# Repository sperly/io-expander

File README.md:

# RS485_IO8 I/O expansion board

An STM32G030-based Modbus RTU I/O expansion board with **8 isolated inputs**
and **8 configurable outputs**. A hardware strap selects RS-485 or RS-232
communication, and a USB-C port (CH340C virtual COM port) gives the same Modbus
link from a PC. Outputs support low-side, high-side, push-pull and PWM modes.

| Directory | Contents |
|---|---|
| [hardware/](hardware/README.md) | Revision B KiCad project, schematics, PCB layout, BOMs, generation and validation tools, and archived revision A files |
| [software/](software/README.md) | C11 firmware, portable Modbus and I/O logic, host unit tests, and a Python Modbus client |

Open `hardware/RS485_IO8.kicad_pro` in KiCad 9 or 10. See the
[hardware README](hardware/README.md) for wiring, straps, electrical limits
and design checks. The schematics are generated; make schematic changes
through the scripts in `hardware/tools/`.

To build and run the host unit tests, install CMake, Ninja and a native C
compiler, then run from the repository root:

```sh
cd software
cmake --preset host-tests
cmake --build --preset host-tests
ctest --preset host-tests
```

Firmware builds also require `arm-none-eabi-gcc` with newlib-nano and ST CMSIS
headers. See the [software README](software/README.md) for toolchain setup,
flashing, the register map and client examples.

The PCB is placed but not routed. The design and firmware have not yet been
tested on hardware; see the subdirectory READMEs for validation status and
remaining prototype checks.

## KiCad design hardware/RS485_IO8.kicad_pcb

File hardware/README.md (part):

# RS485_IO8 — revision B

**8 isolated inputs** (5–24 V, wired as sink or source) and **8 outputs**
(low-side, high-side, push-pull or PWM), with a host link that a strap
switches between **RS-485 (half duplex) and RS-232**, plus a **USB-C port**
(CH340C USB-serial) on the same UART. All parts are
available from LCSC. Open `RS485_IO8.kicad_pro` in KiCad 9 or 10. The
schematic has an overview page and five sheets; `RS485_IO8.pdf` is the
plotted copy.

Firmware: `../software` (Modbus RTU slave, CMake).

## What changed from rev A

| | rev A | rev B |
|---|---|---|
| Schematic | every pin ended in a net label | real wiring inside each functional block, framed blocks, notes and tables on every sheet, overview page with connector/strap tables |
| Host interface | THVD1410 (RS-485 only) | **MAX3160** multiprotocol transceiver, RS-485 or RS-232 set by the **MODE strap** |
| I/O split | 8 combined I/Os (driver output + non-isolated NPN read-back on the same terminal) | **8 dedicated outputs + 8 dedicated isolated inputs** |
| Inputs | 47k/22k + BC847 level shifter, 0–VIO only | **TLP290-4 bidirectional optocouplers**, 5–24 V, two isolated groups with their own COM, sink or source |
| Output driver | DRV8908-Q1 (not stocked at LCSC) | **DRV8912-Q1**, pin-compatible superset; OUT1–OUT8 used, OUT9–OUT12 unconnected |
| USB | – | **USB-C (J11) with CH340C** virtual COM port on the same UART; VBUS can power the board |
| Connectors | 2.54 mm pin headers | **2.54 mm screw terminals** (Xinya XY308) for 5 V, VIO, serial and all I/O |
| Parts | generic | every part has an LCSC number, MPN and manufacturer (`BOM.csv`, `BOM_JLCPCB.csv`) |

Rev A is kept unchanged in `archive/rev_A/`.

## Sheets

1. **Overview**: block flow, connector and strap tables.
2. **Power**: J1 5 V input, AP2112K 3.3 V LDO, J2 + JP1 output supply (VIO) selection, VIO monitor divider.
3. **MCU**: STM32G030F6P6, reset, 24AA02 EEPROM, address straps, SWD header.
4. **Serial**: MAX3160, MODE strap, TVS protection, termination, bias, J4 terminal, J10 DB9;
   USB-C J11 with USBLC6 ESD protection, CH340C and the UART_RX wired-AND.
5. **Driver**: DRV8912-Q1 with decoupling and pull-ups, output terminals J6/J7.
6. **Inputs**: input terminals J8/J9, 2 × TLP290-4 optocouplers, MCP23S08 SPI expander.

## Connectors

All are 2.54 mm screw terminals unless noted.

| Ref | Name | Pins |
|---|---|---|
| J1 | 5V IN | 1 = +5 V, 2 = GND (regulated 4.75–5.25 V) |
| J2 | VIO EXT IN | 1 = EXT_VIO, 2 = GND (4.5–14 V, used with JP1 1-2); top edge, left of J6 |
| J4 | SERIAL | 1 = A, 2 = B / TXD, 3 = RXD, 4 = GND |
| J11 | USB-C | USB 2.0 device (CH340C virtual COM port), 5.1k on CC1/CC2; VBUS can power the board |
| J10 | DB9 SERIAL (female, right angle) | 1 = A, 2 = B / TXD, 3 = RXD, 5 = GND, 6 = +5 V (via JP8), shell = GND; J4 and J10 are in parallel |
| J6 | OUT1-OUT4 | 1 = GND, 2 = VIO, 3 = OUT4, 4 = OUT3, 5 = OUT2, 6 = OUT1 (on the board, left to right: OUT1 … OUT4, VIO, GND) |
| J7 | OUT5-OUT8 | 1 = GND, 2 = VIO, 3 = OUT8, 4 = OUT7, 5 = OUT6, 6 = OUT5 (on the board, left to right: OUT5 … OUT8, VIO, GND) |
| J8 | IN1-IN4 COM1 | 1–4 = IN1–IN4, 5 = COM1 (isolated) |
| J9 | IN5-IN8 COM2 | 1–4 = IN5–IN8, 5 = COM2 (isolated) |
| J3 | SWD | ARM Cortex 10-pin 1.27 mm header (pin header, not a terminal) |
| J5 | FAULT TEST | 2.54 mm header: 1 = DRV8912 nFAULT, 2 = GND |

## Straps

All straps use 2.54 mm shunts.

| Ref | Name | Setting |
|---|---|---|
| JP1 | VIO SELECT | 1-2 = external VIO from J2, 2-3 = on-board +5 V. Fit exactly one shunt and move it only with power removed. |
| JP2 | ADDR0 | fitted = 0 (firmware adds 1 to the address) |
| JP3 | ADDR1 | fitted = 0 (firmware adds 2 to the address) |
| JP4 | MODE | **open = RS-485, fitted = RS-232** |
| JP5 | TERM | 120 Ω across A/B; RS-485 bus ends only |
| JP6 / JP7 | BIAS A / BIAS B | 390 Ω fail-safe bias; fit both on one RS-485 node per bus |
| JP8 | 5V ON PIN 6 | solder jumper, bridged by default: +5 V on DB9 pin 6. Cut it to remove +5 V from the DB9 |

### Serial interface wiring

| J4 pin | DB9 pin | RS-485 (MODE open) | RS-232 (MODE fitted) |
|---|---|---|---|
| 1 | 1 | A (non-inverting) | leave open (unused T2OUT) |
| 2 | 2 | B (inverting) | TXD, output of this board |
| 3 | 3 | – | RXD, input of this board |
| 4 | 5 | GND | GND |
| – | 6 | +5 V (JP8) | +5 V (JP8) |

The DB9 is a female socket with a DCE pinout. A straight (not null-modem)
cable from a PC or USB-RS232 adapter works: the PC transmits on pin 3 and
receives on pin 2. Pin 6 carries the board's +5 V rail. A host can power the
board through it, or the board can supply a small converter. Pin 6 is DSR on
a standard PC port, so **cut JP8** if the DB9 will ever connect to equipment
that drives pin 6.

The MAX3160 shares its driver pins between the two protocols: in RS-232 mode
the B pin carries TXD. **Remove TERM, BIAS A and BIAS B in RS-232 mode**,
otherwise they load TXD. The MAX3160 receiver is fail-safe, so bias is only
needed when other nodes on the bus are not. A/B naming differs between
vendors, so check the polarity against the host.

RS-485 runs half duplex (HDPLX tied high) with the slew-rate-limited driver
(FAST tied low, ≤ 250 kbit/s). DE has a pull-down, so the bus driver stays off
until the firmware enables it. The receiver is always on, and the firmware
discards its own echo.

### USB-C serial

J11 is a USB 2.0 Type-C device port (HRO TYPE-C-31-M-12). A CH340C (U10)
turns it into a virtual COM port on USART1, so the Modbus RTU firmware
works over USB unchanged. Windows 10/11, Linux and macOS have CH34x drivers
built in or available from WCH.

* **Shared UART.** UART_TX drives both the MAX3160 and the CH340C. UART_RX is
  a wired-AND: D5 (BAT54A, common anode) and the 4.7 kΩ pull-up R44 combine
  the MAX3160 receiver output and the CH340C TXD, so either one can pull
  the line low. Both host links are always live, so **use only one host at a
  time**. In RS-485 mode, traffic from other bus nodes would collide with
  USB data. Replies to a USB host also go out on RS-485 / RS-232. The
  pull-up and diode drop are fine up to 115 200 baud.
* **Power from USB.** VBUS reaches the +5V rail through D4 (B5819W, about
  4.6 V at the rail), so the board runs from USB alone. J1 and USB can both
  be connected: the higher supply wins and D4 blocks back-feeding into the
  PC. USB supplies at most 500 mA by default (5.1 kΩ CC pull-downs). With
  JP1 at 2-3, VIO also comes from this rail, so keep output loads small when
  running from USB.
* U9 (USBLC6-2SC6) protects D+, D− and VBUS. The shield is tied to GND.
* The CH340C runs from +3V3 (V3 tied to VCC), so its I/O matches the STM32.
  CTS, DSR, RI, DCD, DTR and RTS are not used.

## Inputs: sink or source

Each input is a bidirectional opto LED with a 3.3 kΩ series resistor, wired
between the INx pin and the group's COM pin. Current in either direction
makes the input active, so the polarity is chosen by wiring COM. No strap is
needed:

| Field device | Connect COM to | Input is active when |
|---|---|---|
| PNP sensor / switch to +V (source) | GND of the field supply | INx is connected to +V |
| NPN sensor / switch to GND (sink) | +V of the field supply | INx is connected to GND |

* IN1–IN4 / COM1 and IN5–IN8 / COM2 are two separate groups. Each group can
  be wired either way, and each can use its own field supply.
* 5–24 V nominal (30 V max). On above about 4 V, off below about 2 V. A
  4.7 kΩ shunt across each LED makes small leakage currents read as off.
* Input current is about 0.9 mA at 5 V and 6.6 mA at 24 V. The series
  resistor is a 1206 / 0.25 W part.
* The field side is galvanically isolated from the logic (TLP290-4, 2.5 kVrms).
  Keep field-side copper away from logic copper in the layout.
* Active = 1 in firmware. A per-input invert setting covers normally-closed
  contacts.

## Outputs

* Each output can be off, a low-side switch (to GND), a high-side switch (to
  VIO) or push-pull, optionally with PWM. Loads return to the VIO / GND pins
  of the same terminal. VIO is 4.5–14 V (JP1).
* **PWM:** the DRV8912 has 4 PWM generators (80 / 100 / 200 / 2000 Hz,
  8-bit duty). All eight outputs can use PWM, but they share at most four
  duty/frequency settings.
* Don't drive an output from outside above VIO or below GND (body diodes).
  The output side has no isolation, reverse-polarity or load-dump protection.

## PCB

`RS485_IO8.kicad_pcb` is placed but **not routed**. It's 82 × 68 mm, 4 layers:

| Layer | Use |
|---|---|
| F.Cu | signals, components |
| In1.Cu "GND" | GND plane (zone, filled) |
| In2.Cu "PWR" | +3V3 plane (zone, filled); route VIO / +5V as wide traces |
| B.Cu | signals |

KiCad applies its default 1.6 mm 4-layer stack-up. Set the real one under
*Board Setup → Physical Stackup* to match the board house (e.g. JLCPCB
JLC04161H-7628).

* **Left edge:** DB9 J10 directly above USB-C J11, the pair centred on the
  edge. The DB9 pin-6 jumper JP8 sits next to the DB9. The ESD array U9,
  VBUS diode D4, CC resistors and the CH340C U10 sit between J11 and the
  LDO. The UART_RX wired-AND (D5, R44) sits below the MAX3160.
* **Top edge:** VIO input J2, then output terminals J6 and J7, with the
  DRV8912 and its capacitors right below them. Left to right the edge reads
  GND VIO | OUT1 OUT2 OUT3 OUT4 VIO GND | OUT5 OUT6 OUT7 OUT8 VIO GND. The
  terminal pin numbers run the other way (J6/J7 pin 1 = GND, J2 pin 1 =
  VIO), because a top-edge terminal with its wire entry facing out has pin 1
  on the right. The VIO select strap JP1 sits next to J2, so the external
  VIO path stays short; route VIO (JP1 → DRV8912 VM, J6/J7 VIO pins) and
  the +5V feed to JP1 pin 3 as wide traces.
* **Bottom edge:** power terminal J1 (+5 V) and serial terminal J4 on the
  left, isolated input terminals J8 (IN1–4, COM1) and J9 (IN5–8, COM2) on
  the right. Each input is one straight column: terminal pin → 3.3k series
  resistor → 4.7k shunt → opto LED, with the opto's phototransistor and
  22k pull-up directly above it.
* **Middle:** MAX3160 with protection, termination/bias jumpers and the MODE
  strap; LDO; STM32 with the VIO monitor divider next to its ADC pin,
  EEPROM, SWD header (J3), address straps and the MCP23S08.
* **Mounting holes:** 4 × M3 in the corners, 4 mm from both edges.
* The terminals sit on the long edges, so the board doesn't fit standard
  Eurocard card guides.
* **Isolation barrier:** drawn on Dwgs.User along the opto centre line
  (y = 42.5 mm from the top edge) and down at x = 42 mm. A rule area
  `ISOLATED_FIELD` blocks zone fills on all copper layers below / right of
  it, so neither plane reaches the field side. Inside that area route only
  terminal → series resistor → shunt → opto LED, and no logic traces.
* Pin labels for every terminal are on the silkscreen (the edge terminals
  carry no reference text; their pin labels identify them). Terminal wire
  entries face the board edge.
* DRC with schematic parity: 0 errors. The only warnings are 2 USB-C silk
  lines that cross the board edge, which is normal for an edge connector,
  plus the unrouted connections. Footprints carry the
  LCSC/MPN/datasheet fields and are linked to the schematic, so *Update PCB
  from Schematic* keeps the placement.
* Check the DB9 footprint
  (`DSUB-9_Socket_Horizontal_P2.77x2.84mm_EdgePinOffset7.70mm_Housed_MountingHolesOffset9.12mm`)
  against the D-DMR009PF-D002 datasheet before ordering. Pin row to edge
  is 7.7 mm, and the board-lock holes are 25 mm apart and 9.12 mm from the
  edge.

## Part choices

All parts are LCSC-sourced. Stock is from the LCSC/JLCPCB catalogue snapshot
of 2026-11-17.

| Ref | Part | LCSC | Stock | Note |
|---|---|---|---|---|
| U1 | AP2112K-3.3TRG1 | C51118 | 12.5k | 600 mA LDO |
| U2 | STM32G030F6P6 | C724040 | 2.2k | |
| U3 | 24AA02T-I/OT | C478090 | 608 | |
| U4 | MAX3160EAP+T | C406604 | 4.1k | about $4.90, the most expensive part |
| U5 | DRV8912QPWPRQ1 | C1855817 | 2.4k | footprint with thermal vias |
| U6, U7 | TLP290-4(GB-TP,E | C39031 | 15.9k | quad AC-input opto, CTR 100–400 % |
| U8 | MCP23S08T-E/SS | C145600 | 389 | lowest stock; MCP23S08-E/SS C144204 is the same die |
| J8, J9 | XY308-2.54-5P | C915914 | 6.3k | |
| D2 | SM712 | C7420375 | 539k | RS-485 TVS |
| D3 | H15VND3B | C20615813 | 803k | 15 V bidirectional TVS, RS-232 RXD |
| J1, J2 | XY308-2.54-2P | C557685 | 5.6k | |
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
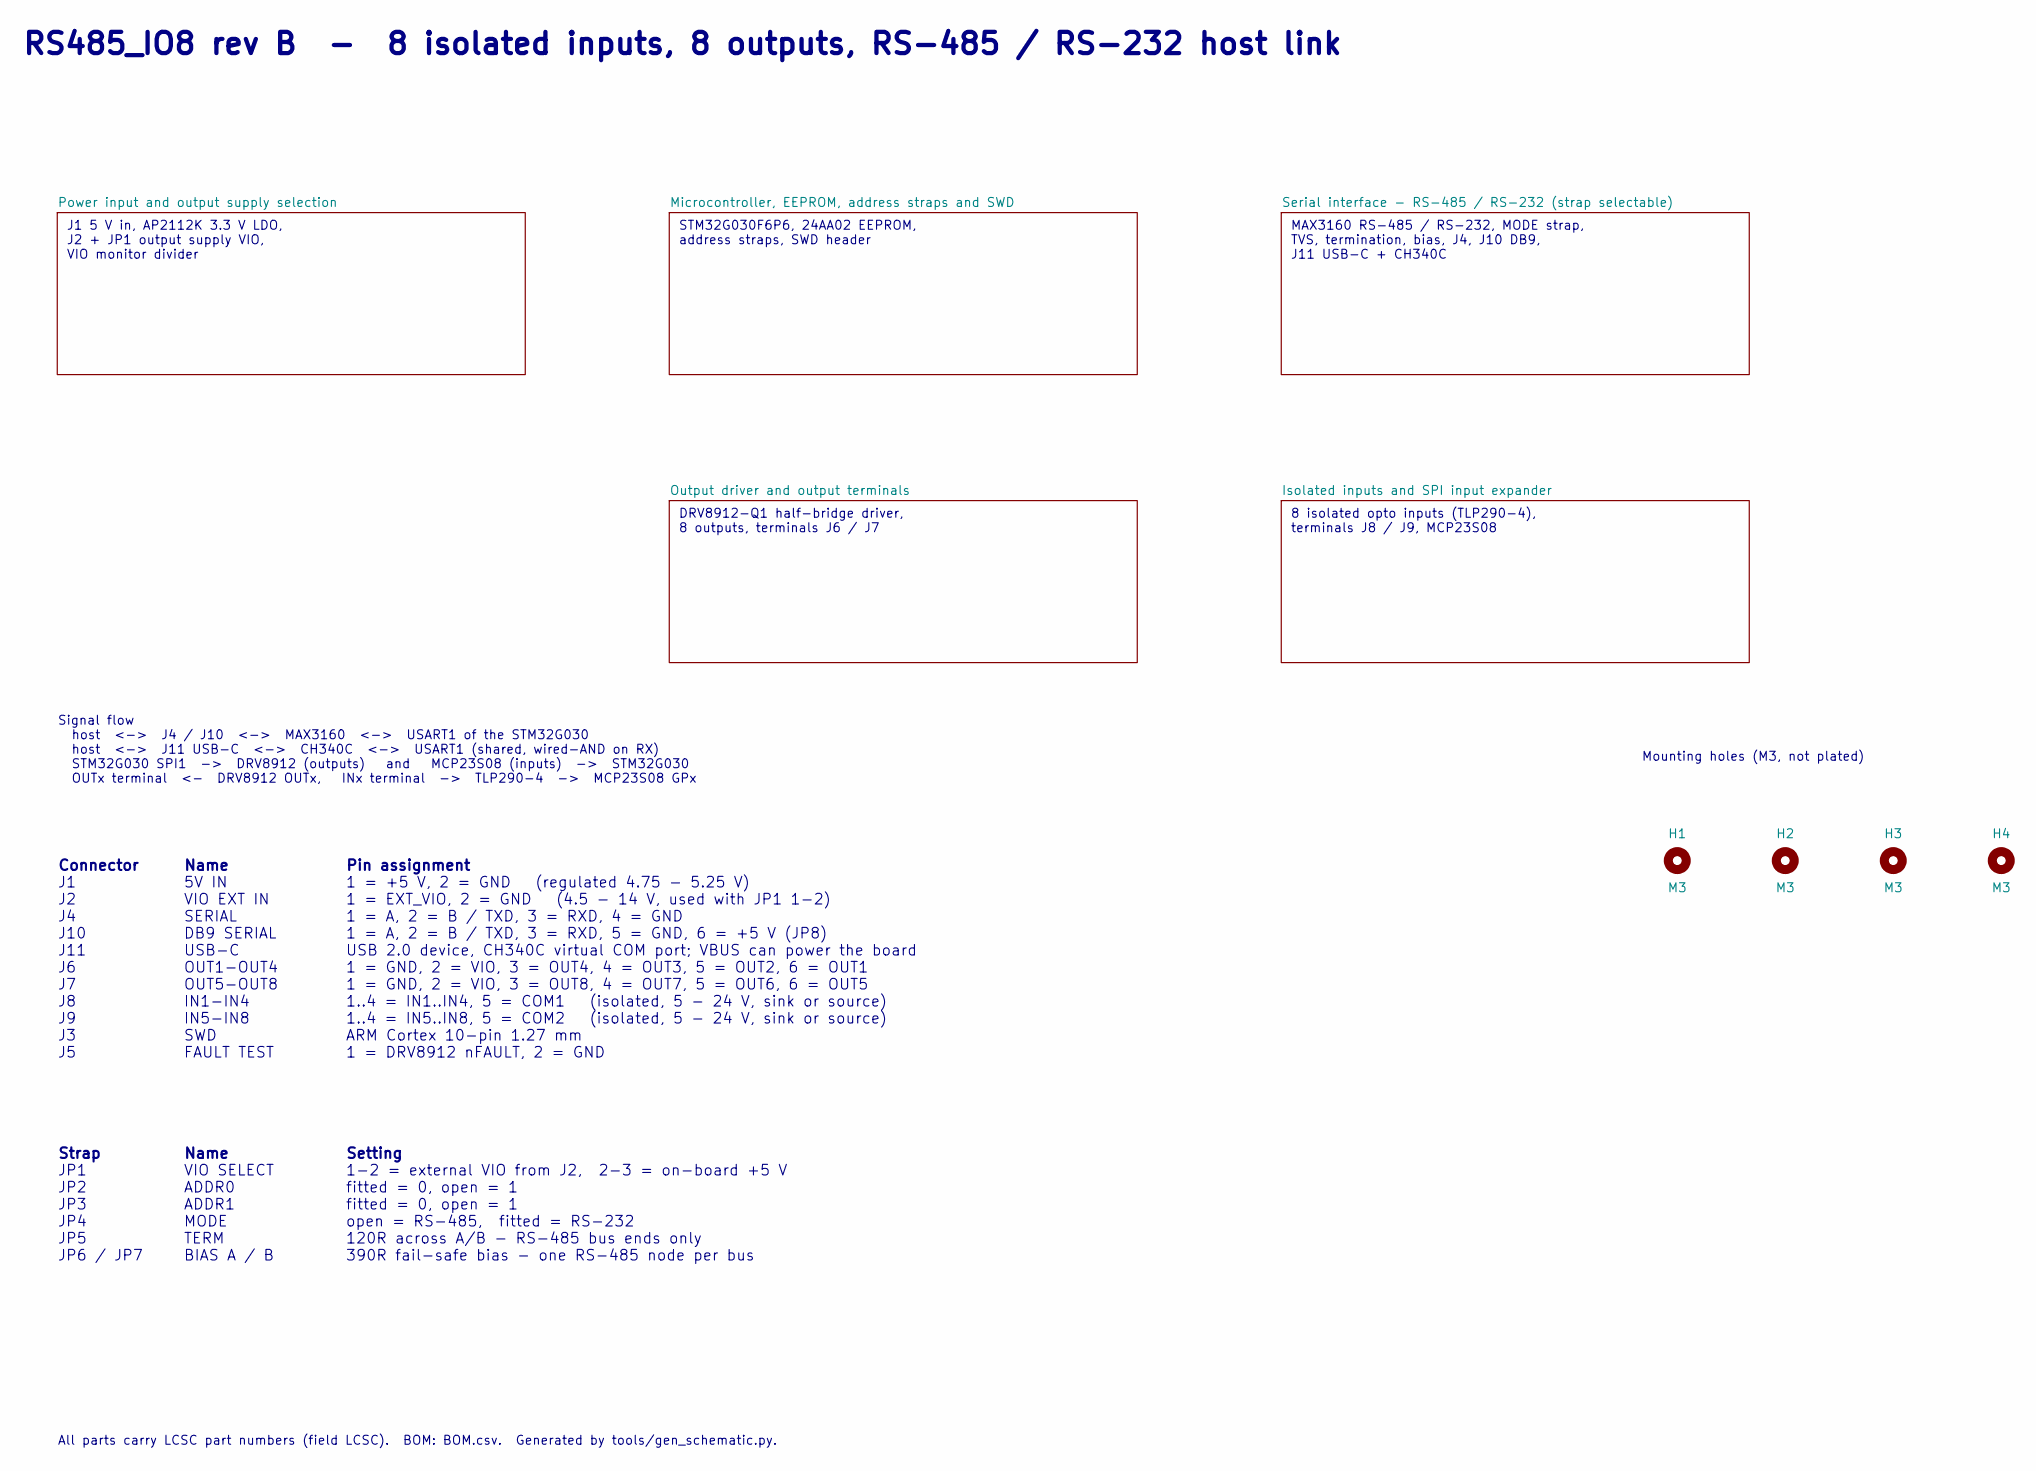
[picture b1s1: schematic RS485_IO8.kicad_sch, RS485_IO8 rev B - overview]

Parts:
H1, H2, H3, H4: M3; MountingHole_3.2mm_M3

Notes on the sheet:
fitted = 0, open = 1
1 = EXT_VIO, 2 = GND (4.5 - 14 V, used with JP1 1-2)
J10
All parts carry LCSC part numbers (field LCSC). BOM: BOM.csv. Generated by tools/gen_schematic.py.
1 = A, 2 = B / TXD, 3 = RXD, 5 = GND, 6 = +5 V (JP8)
JP2
Name
1 = GND, 2 = VIO, 3 = OUT8, 4 = OUT7, 5 = OUT6, 6 = OUT5
DRV8912-Q1 half-bridge driver, 8 outputs, terminals J6 / J7
Setting
J11
Pin assignment
1 = DRV8912 nFAULT, 2 = GND
ARM Cortex 10-pin 1.27 mm
ADDR1
1..4 = IN1..IN4, 5 = COM1 (isolated, 5 - 24 V, sink or source)
open = RS-485, fitted = RS-232
VIO SELECT
1 = A, 2 = B / TXD, 3 = RXD, 4 = GND
USB-C
JP1
1 = GND, 2 = VIO, 3 = OUT4, 4 = OUT3, 5 = OUT2, 6 = OUT1
Signal flow host <-> J4 / J10 <-> MAX3160 <-> USART1 of the STM32G030 host <-> J11 USB-C <-> CH340C <-> USART1 (shared, wired-AND on RX) STM32G030 SPI1 -> DRV8912 (outputs) and MCP23S08 (inputs) -> STM32G030 OUTx terminal <- DRV8912 OUTx, INx terminal -> TLP290-4 -> MCP23S08 GPx
5V IN
J1 5 V in, AP2112K 3.3 V LDO, J2 + JP1 output supply VIO, VIO monitor divider
1 = +5 V, 2 = GND (regulated 4.75 - 5.25 V)
TERM
Mounting holes (M3, not plated)
JP5
BIAS A / B
OUT5-OUT8
FAULT TEST
MODE
MAX3160 RS-485 / RS-232, MODE strap, TVS, termination, bias, J4, J10 DB9, J11 USB-C + CH340C
390R fail-safe bias - one RS-485 node per bus
8 isolated opto inputs (TLP290-4), terminals J8 / J9, MCP23S08
SERIAL
DB9 SERIAL
SWD
STM32G030F6P6, 24AA02 EEPROM, address straps, SWD header

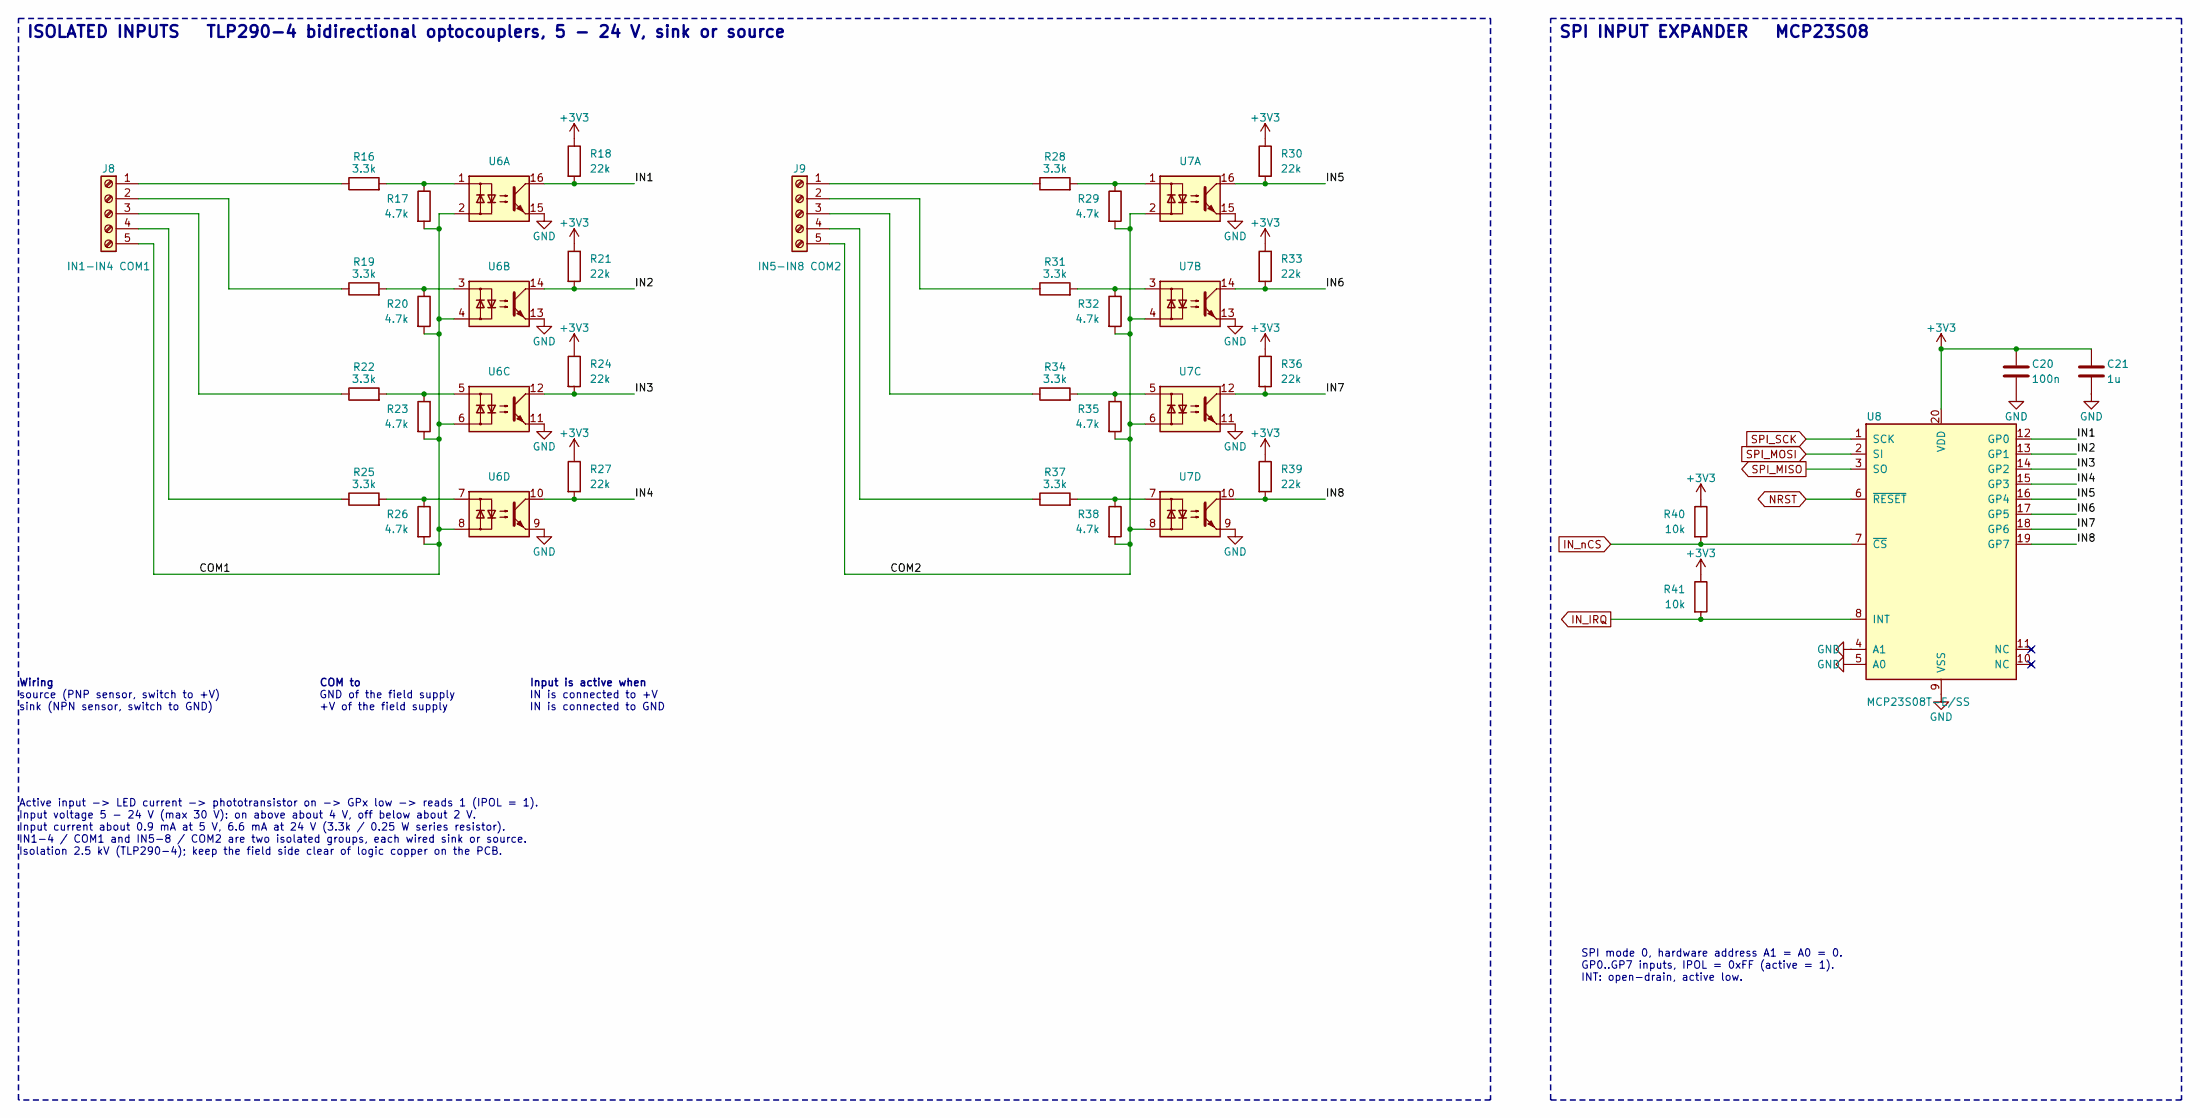
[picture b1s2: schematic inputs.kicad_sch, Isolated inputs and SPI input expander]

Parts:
C20: 100n; C_0603_1608Metric; MPN CC0603KRX7R9BB104; LCSC C14663
C21: 1u; C_0603_1608Metric; MPN CL10A105KB8NNNC; LCSC C15849
J8: IN1-IN4 COM1; TerminalBlock_Xinya_XY308-2.54-5P_1x05_P2.54mm_Horizontal; MPN XY308-2.54-5P; LCSC C915914
J9: IN5-IN8 COM2; TerminalBlock_Xinya_XY308-2.54-5P_1x05_P2.54mm_Horizontal; MPN XY308-2.54-5P; LCSC C915914
R16, R19, R22, R25, R28, R31, R34, R37: 3.3k; R_1206_3216Metric; MPN 1206W4F3301T5E; LCSC C26032
R17, R20, R23, R26, R29, R32, R35, R38: 4.7k; R_0603_1608Metric; MPN 0603WAF4701T5E; LCSC C23162
R18, R21, R24, R27, R30, R33, R36, R39: 22k; R_0603_1608Metric; MPN 0603WAF2202T5E; LCSC C31850
R40, R41: 10k; R_0603_1608Metric; MPN 0603WAF1002T5E; LCSC C25804
U6, U7: TLP290-4; SOP-16_4.55x10.3mm_P1.27mm; MPN TLP290-4(GB-TP,E; LCSC C39031
U8: MCP23S08T-E/SS; SSOP-20_5.3x7.2mm_P0.65mm; MPN MCP23S08T-E/SS; LCSC C145600

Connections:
+3V3: C20.1, C21.1, R18.1, R21.1, R24.1, R27.1, R30.1, R33.1, R36.1, R39.1, R40.1, R41.1, U8.20 (VDD); also elsewhere on the board
/Isolated inputs and SPI input expander/COM1: J8.5, R17.2, R20.2, R23.2, R26.2, U6.2, U6.4, U6.6, U6.8
/Isolated inputs and SPI input expander/COM2: J9.5, R29.2, R32.2, R35.2, R38.2, U7.2, U7.4, U7.6, U7.8
/Isolated inputs and SPI input expander/IN1: R18.2, U6.16, U8.12 (GP0)
/Isolated inputs and SPI input expander/IN2: R21.2, U6.14, U8.13 (GP1)
/Isolated inputs and SPI input expander/IN3: R24.2, U6.12, U8.14 (GP2)
/Isolated inputs and SPI input expander/IN4: R27.2, U6.10, U8.15 (GP3)
/Isolated inputs and SPI input expander/IN5: R30.2, U7.16, U8.16 (GP4)
/Isolated inputs and SPI input expander/IN6: R33.2, U7.14, U8.17 (GP5)
/Isolated inputs and SPI input expander/IN7: R36.2, U7.12, U8.18 (GP6)
/Isolated inputs and SPI input expander/IN8: R39.2, U7.10, U8.19 (GP7)
IN_IRQ: R41.2, U8.8 (INT); also elsewhere on the board
IN_nCS: R40.2, U8.7 (~CS); also elsewhere on the board
NRST: U8.6 (~RESET); also elsewhere on the board
unnamed: J8.1, R16.1
unnamed: J8.2, R19.1
unnamed: J8.3, R22.1
unnamed: J8.4, R25.1
unnamed: J9.1, R28.1
unnamed: J9.2, R31.1
unnamed: J9.3, R34.1
unnamed: J9.4, R37.1
unnamed: R16.2, R17.1, U6.1
unnamed: R19.2, R20.1, U6.3
unnamed: R22.2, R23.1, U6.5
unnamed: R25.2, R26.1, U6.7
unnamed: R28.2, R29.1, U7.1
unnamed: R31.2, R32.1, U7.3
unnamed: R34.2, R35.1, U7.5
unnamed: R37.2, R38.1, U7.7
SPI_MISO: U8.3 (SO); also elsewhere on the board
SPI_MOSI: U8.2 (SI); also elsewhere on the board
SPI_SCK: U8.1 (SCK); also elsewhere on the board

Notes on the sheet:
GND of the field supply
Active input -> LED current -> phototransistor on -> GPx low -> reads 1 (IPOL = 1). Input voltage 5 - 24 V (max 30 V): on above about 4 V, off below about 2 V. Input current about 0.9 mA at 5 V, 6.6 mA at 24 V (3.3k / 0.25 W series resistor). IN1-4 / COM1 and IN5-8 / COM2 are two isolated groups, e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
sink (NPN sensor, switch to GND)
IN is connected to GND
COM to
Input is active when
ISOLATED INPUTS TLP290-4 bidirectional optocouplers, 5 - 24 V, sink or source
SPI mode 0, hardware address A1 = A0 = 0. GP0..GP7 inputs, IPOL = 0xFF (active = 1). INT: open-drain, active low.
Wiring
source (PNP sensor, switch to +V)
IN is connected to +V
SPI INPUT EXPANDER MCP23S08
+V of the field supply

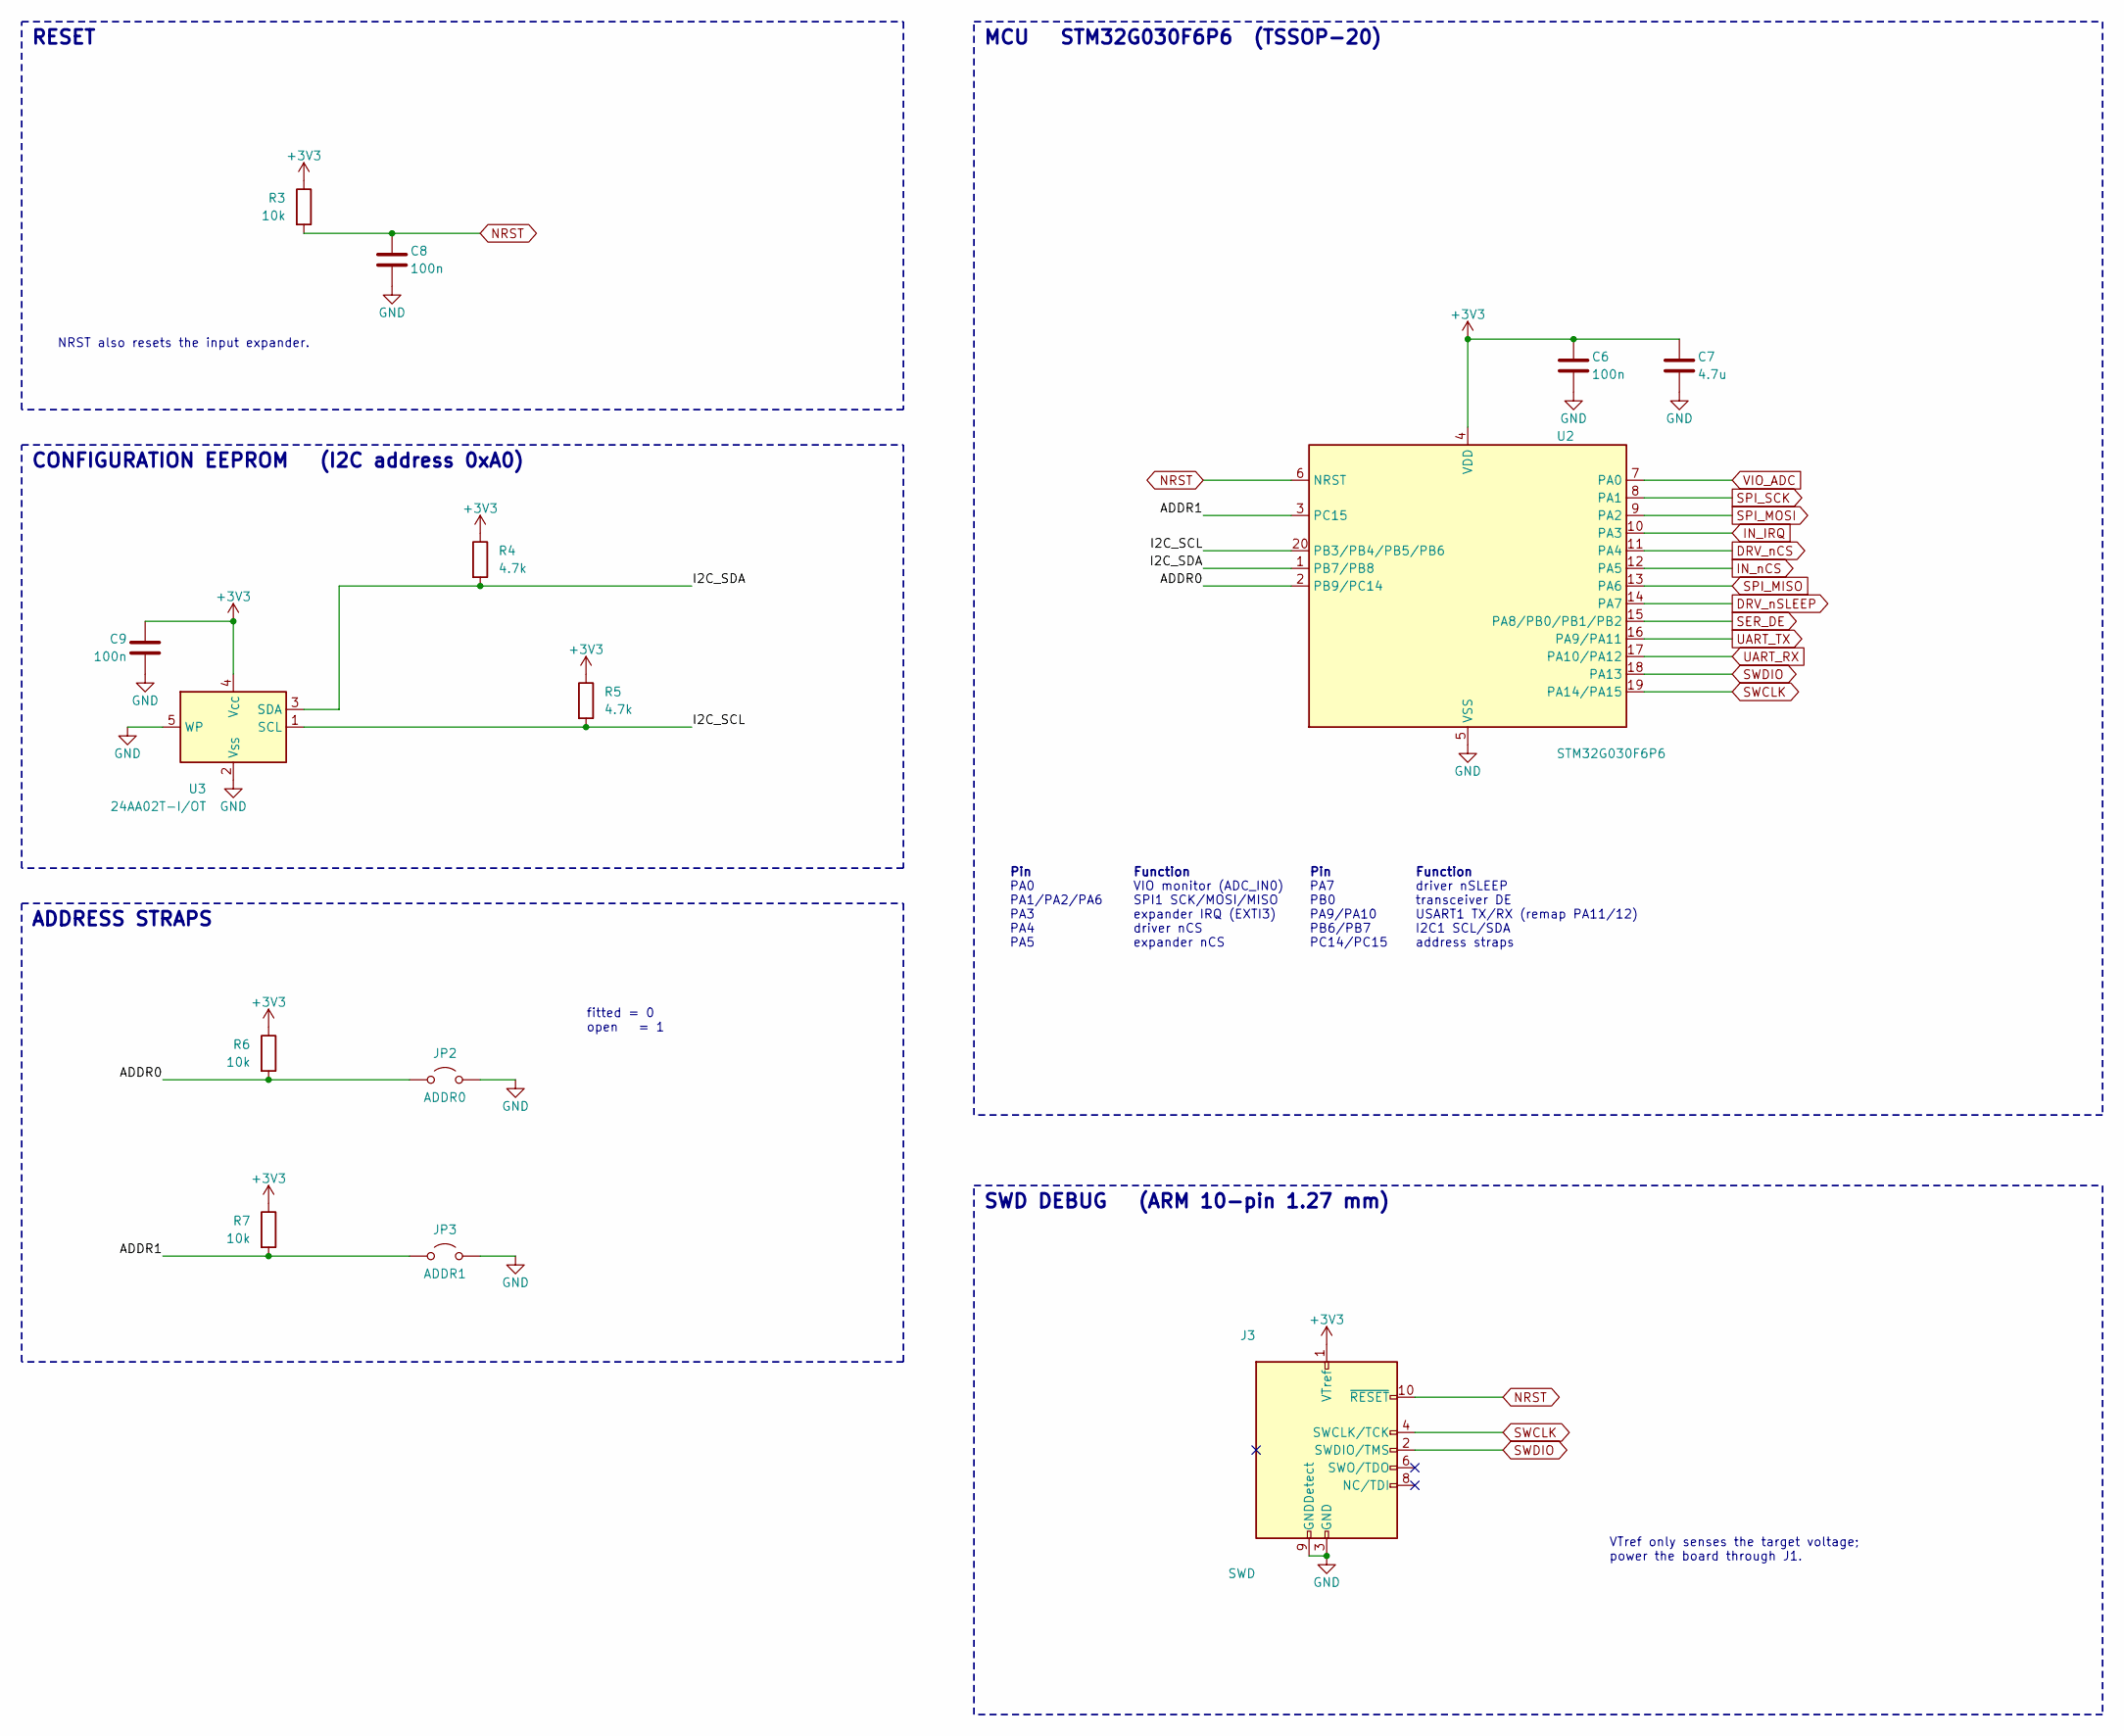
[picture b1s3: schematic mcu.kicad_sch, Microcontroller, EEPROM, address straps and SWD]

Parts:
C6, C8, C9: 100n; C_0603_1608Metric; MPN CC0603KRX7R9BB104; LCSC C14663
C7: 4.7u; C_0603_1608Metric; MPN CL10A475KO8NNNC; LCSC C19666
J3: SWD; PinHeader_2x05_P1.27mm_Vertical; MPN A127M01-0B10P51-H10A39; LCSC C41426986
JP2: ADDR0; PinHeader_1x02_P2.54mm_Vertical; MPN PZ254V-11-02P; LCSC C492401
JP3: ADDR1; PinHeader_1x02_P2.54mm_Vertical; MPN PZ254V-11-02P; LCSC C492401
R3, R6, R7: 10k; R_0603_1608Metric; MPN 0603WAF1002T5E; LCSC C25804
R4, R5: 4.7k; R_0603_1608Metric; MPN 0603WAF4701T5E; LCSC C23162
U2: STM32G030F6P6; TSSOP-20_4.4x6.5mm_P0.65mm; MPN STM32G030F6P6; LCSC C724040
U3: 24AA02T-I/OT; SOT-23-5; MPN 24AA02T-I/OT; LCSC C478090

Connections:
+3V3: C6.1, C7.1, C9.1, J3.1 (VTref), R3.1, R4.1, R5.1, R6.1, R7.1, U2.4 (VDD), U3.4 (V_{CC}); also elsewhere on the board
/Microcontroller, EEPROM, address straps and SWD/ADDR0: JP2.1 (A), R6.2, U2.2 (PB9/PC14)
/Microcontroller, EEPROM, address straps and SWD/ADDR1: JP3.1 (A), R7.2, U2.3 (PC15)
/Microcontroller, EEPROM, address straps and SWD/I2C_SCL: R5.2, U2.20 (PB3/PB4/PB5/PB6), U3.1 (SCL)
/Microcontroller, EEPROM, address straps and SWD/I2C_SDA: R4.2, U2.1 (PB7/PB8), U3.3 (SDA)
DRV_nCS: U2.11 (PA4); also elsewhere on the board
DRV_nSLEEP: U2.14 (PA7); also elsewhere on the board
IN_IRQ: U2.10 (PA3); also elsewhere on the board
IN_nCS: U2.12 (PA5); also elsewhere on the board
NRST: C8.1, J3.10 (~RESET), R3.2, U2.6 (NRST); also elsewhere on the board
SER_DE: U2.15 (PA8/PB0/PB1/PB2); also elsewhere on the board
SPI_MISO: U2.13 (PA6); also elsewhere on the board
SPI_MOSI: U2.9 (PA2); also elsewhere on the board
SPI_SCK: U2.8 (PA1); also elsewhere on the board
SWCLK: J3.4 (SWCLK/TCK), U2.19 (PA14/PA15)
SWDIO: J3.2 (SWDIO/TMS), U2.18 (PA13)
UART_RX: U2.17 (PA10/PA12); also elsewhere on the board
UART_TX: U2.16 (PA9/PA11); also elsewhere on the board
VIO_ADC: U2.7 (PA0); also elsewhere on the board

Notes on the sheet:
driver nCS
USART1 TX/RX (remap PA11/12)
expander nCS
PA5
PB6/PB7
VIO monitor (ADC_IN0)
address straps
expander IRQ (EXTI3)
SPI1 SCK/MOSI/MISO
PB0
PA0
fitted = 0 open = 1
PC14/PC15
Pin
PA4
PA7
driver nSLEEP
SWD DEBUG (ARM 10-pin 1.27 mm)
PA9/PA10
PA3
transceiver DE
RESET
Function
MCU STM32G030F6P6 (TSSOP-20)
NRST also resets the input expander.
CONFIGURATION EEPROM (I2C address 0xA0)
ADDRESS STRAPS
PA1/PA2/PA6
I2C1 SCL/SDA
VTref only senses the target voltage; power the board through J1.

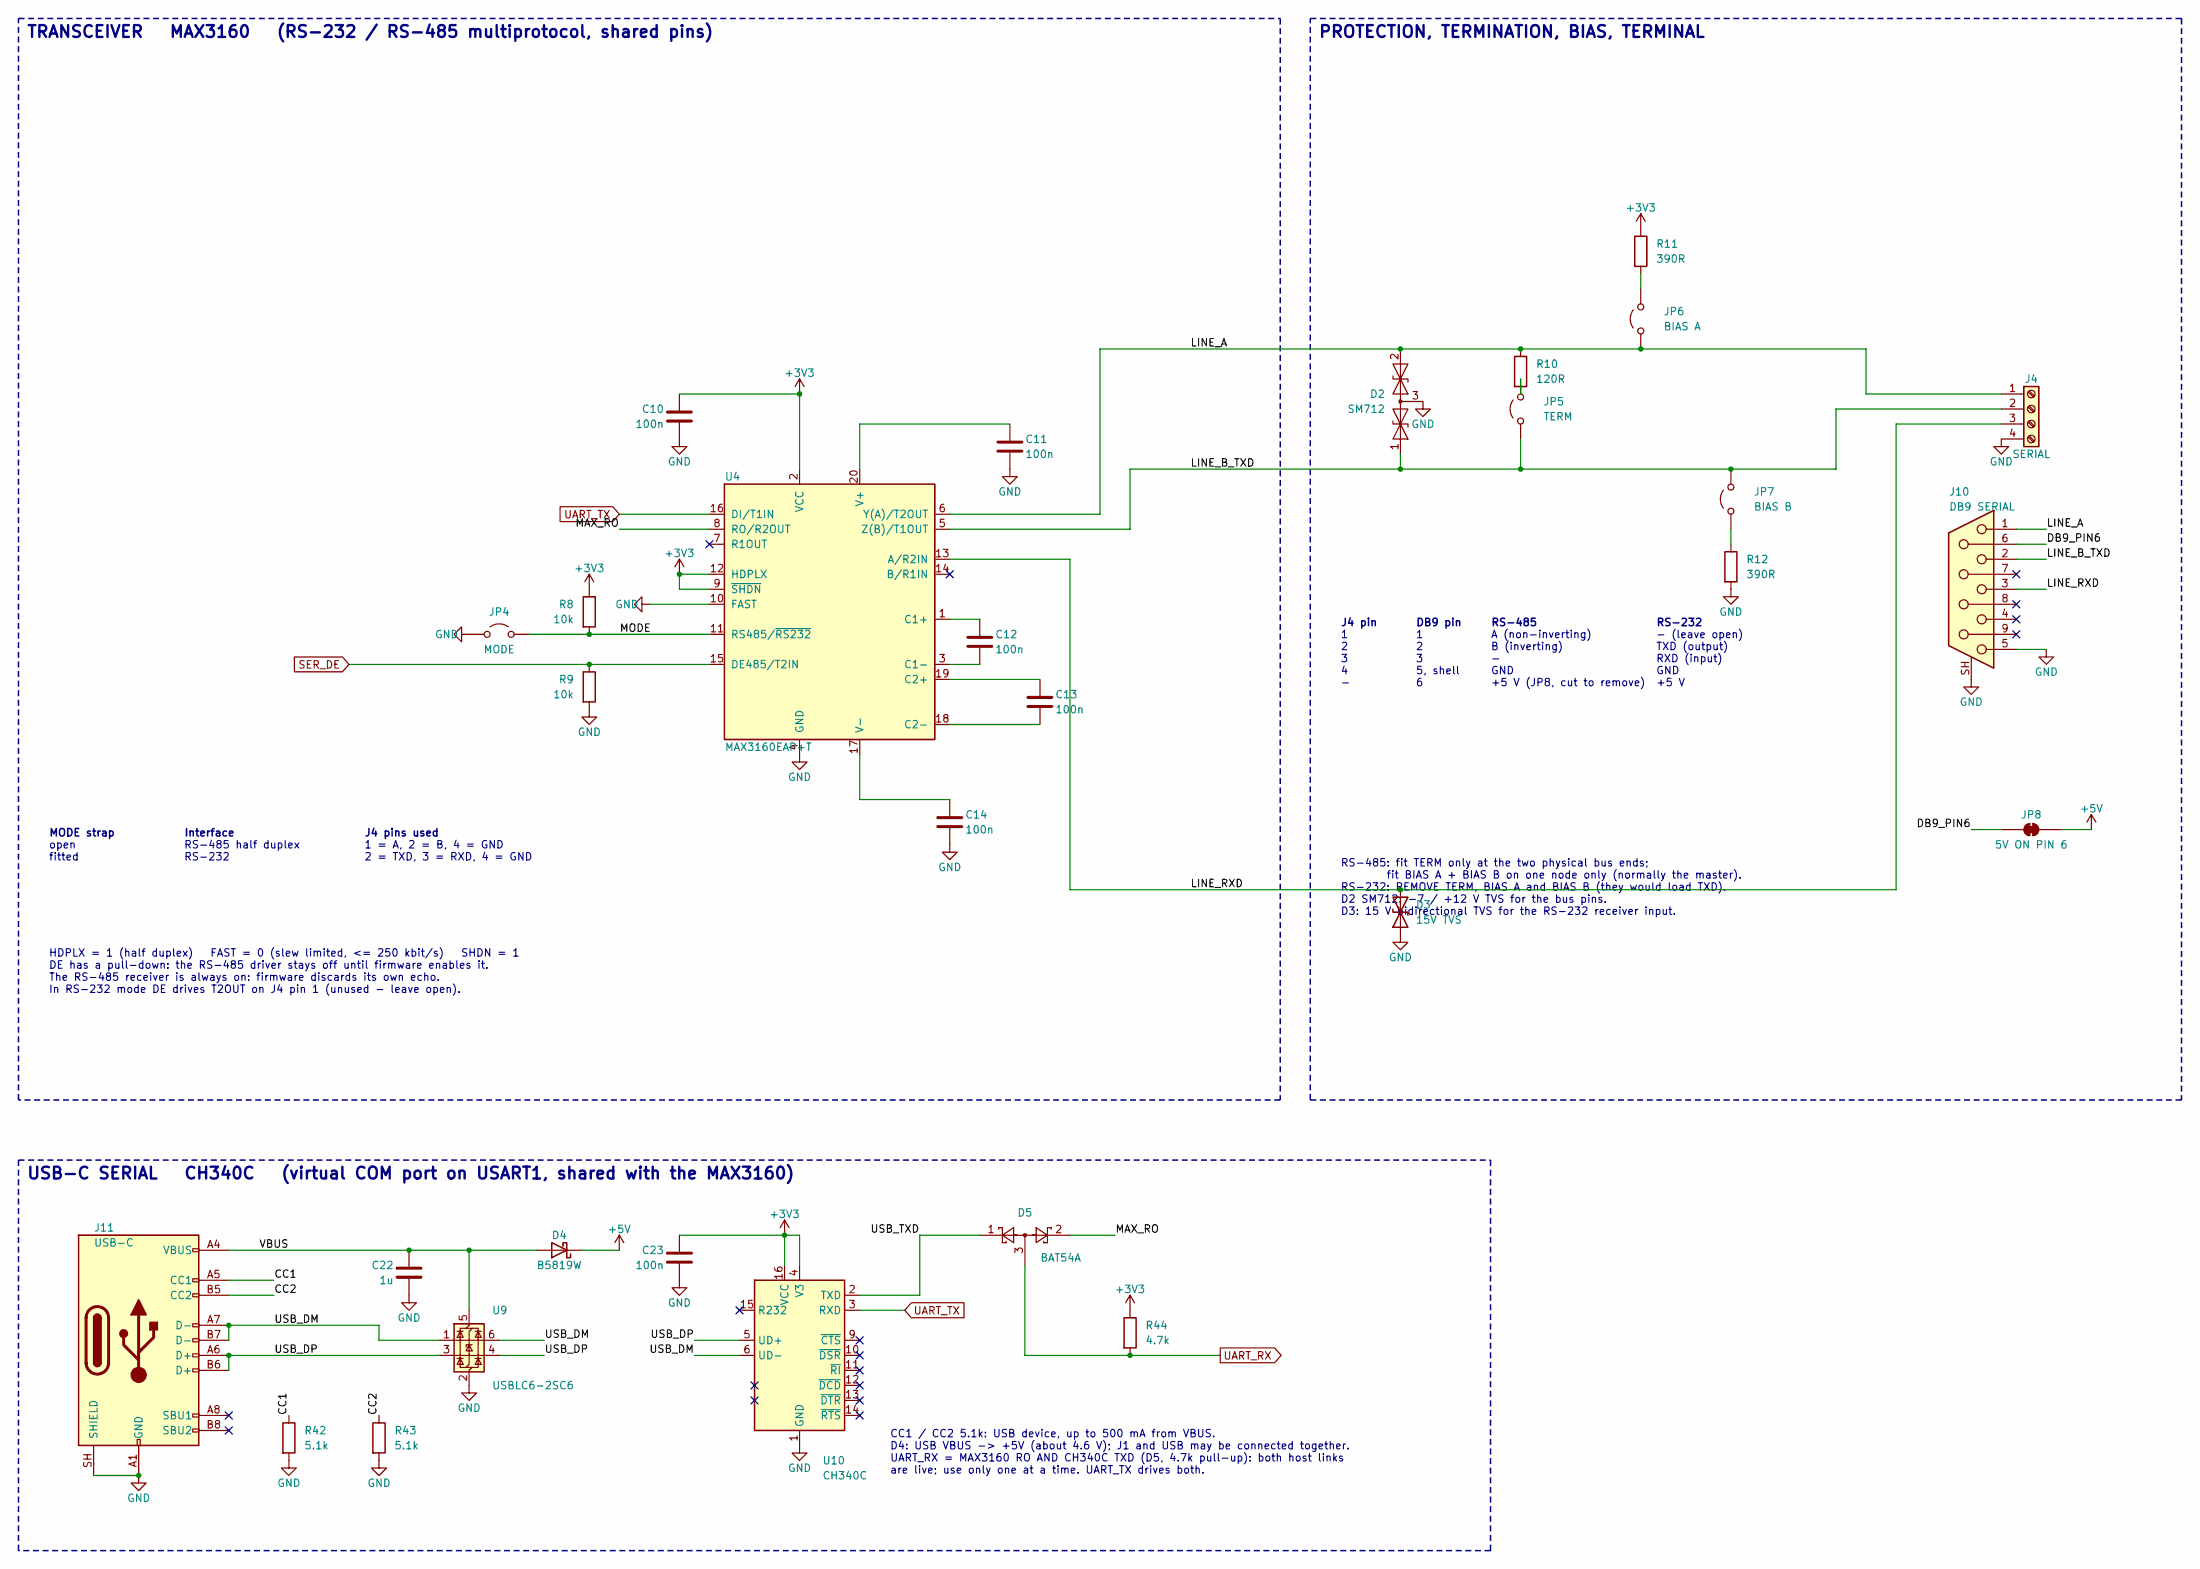
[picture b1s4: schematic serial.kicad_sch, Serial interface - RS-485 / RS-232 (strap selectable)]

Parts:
C10, C11, C12, C13, C14, C23: 100n; C_0603_1608Metric; MPN CC0603KRX7R9BB104; LCSC C14663
C22: 1u; C_0603_1608Metric; MPN CL10A105KB8NNNC; LCSC C15849
D2: SM712; SOT-23; MPN SM712; LCSC C7420375
D3: 15V TVS; D_SOD-323; MPN H15VND3B; LCSC C20615813
D4: B5819W; D_SOD-123; MPN B5819W SL; LCSC C8598
D5: BAT54A; SOT-23; MPN BAT54A,215; LCSC C130910
J4: SERIAL; TerminalBlock_Xinya_XY308-2.54-4P_1x04_P2.54mm_Horizontal; MPN XY308-2.54-4P; LCSC C915913
J10: DB9 SERIAL; DSUB-9_Socket_Horizontal_P2.77x2.84mm_EdgePinOffset7.70mm_H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; MPN D-DMR009PF-D002; LCSC C141882
J11: USB-C; USB_C_Receptacle_HRO_TYPE-C-31-M-12; MPN TYPE-C-31-M-12; LCSC C165948
JP4: MODE; PinHeader_1x02_P2.54mm_Vertical; MPN PZ254V-11-02P; LCSC C492401
JP5: TERM; PinHeader_1x02_P2.54mm_Vertical; MPN PZ254V-11-02P; LCSC C492401
JP6: BIAS A; PinHeader_1x02_P2.54mm_Vertical; MPN PZ254V-11-02P; LCSC C492401
JP7: BIAS B; PinHeader_1x02_P2.54mm_Vertical; MPN PZ254V-11-02P; LCSC C492401
JP8: 5V ON PIN 6; SolderJumper-2_P1.3mm_Bridged_RoundedPad1.0x1.5mm
R8, R9: 10k; R_0603_1608Metric; MPN 0603WAF1002T5E; LCSC C25804
R10: 120R; R_1206_3216Metric; MPN 1206W4F1200T5E; LCSC C17909
R11, R12: 390R; R_0603_1608Metric; MPN 0603WAF3900T5E; LCSC C23151
R42, R43: 5.1k; R_0603_1608Metric; MPN 0603WAF5101T5E; LCSC C23186
R44: 4.7k; R_0603_1608Metric; MPN 0603WAF4701T5E; LCSC C23162
U4: MAX3160EAP+T; SSOP-20_5.3x7.2mm_P0.65mm; MPN MAX3160EAP+T; LCSC C406604
U9: USBLC6-2SC6; SOT-23-6; MPN USBLC6-2SC6; LCSC C2687116
U10: CH340C; SOIC-16_3.9x9.9mm_P1.27mm; MPN CH340C; LCSC C84681

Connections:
+3V3: C10.1, C23.1, R8.1, R11.1, R44.1, U4.2 (VCC), U4.9 (~SHDN), U4.12 (HDPLX), U10.4 (V3), U10.16 (VCC); also elsewhere on the board
/Serial interface - RS-485 / RS-232 (strap selectable)/CC1: J11.A5 (CC1), R42.1
/Serial interface - RS-485 / RS-232 (strap selectable)/CC2: J11.B5 (CC2), R43.1
/Serial interface - RS-485 / RS-232 (strap selectable)/DB9_PIN6: J10.6, JP8.1 (A)
/Serial interface - RS-485 / RS-232 (strap selectable)/LINE_A: D2.2 (A2), J4.1, J10.1, JP6.1 (A), R10.1, U4.6 (Y(A)/T2OUT)
/Serial interface - RS-485 / RS-232 (strap selectable)/LINE_B_TXD: D2.1 (A1), J4.2, J10.2, JP5.1 (A), JP7.2 (B), U4.5 (Z(B)/T1OUT)
/Serial interface - RS-485 / RS-232 (strap selectable)/LINE_RXD: D3.2 (A2), J4.3, J10.3, U4.13 (A/R2IN)
/Serial interface - RS-485 / RS-232 (strap selectable)/MAX_RO: D5.2, U4.8 (RO/R2OUT)
/Serial interface - RS-485 / RS-232 (strap selectable)/MODE: JP4.2 (B), R8.2, U4.11 (RS485/~RS232)
/Serial interface - RS-485 / RS-232 (strap selectable)/USB_DM: J11.A7 (D-), J11.B7 (D-), U9.1 (I/O1), U9.6 (I/O1), U10.6 (UD-)
/Serial interface - RS-485 / RS-232 (strap selectable)/USB_DP: J11.A6 (D+), J11.B6 (D+), U9.3 (I/O2), U9.4 (I/O2), U10.5 (UD+)
/Serial interface - RS-485 / RS-232 (strap selectable)/USB_TXD: D5.1, U10.2 (TXD)
/Serial interface - RS-485 / RS-232 (strap selectable)/VBUS: C22.1, D4.2 (A), J11.A4 (VBUS), J11.A9 (VBUS), J11.B4 (VBUS), J11.B9 (VBUS), U9.5 (VBUS)
unnamed: JP5.2 (B), R10.2
unnamed: JP6.2 (B), R11.2
unnamed: JP7.1 (A), R12.1
unnamed: C12.1, U4.1 (C1+)
unnamed: C12.2, U4.3 (C1-)
unnamed: C13.1, U4.19 (C2+)
unnamed: C13.2, U4.18 (C2-)
unnamed: C11.1, U4.20 (V+)
unnamed: C14.1, U4.17 (V-)
SER_DE: R9.1, U4.15 (DE485/T2IN); also elsewhere on the board
UART_RX: D5.3, R44.2; also elsewhere on the board
UART_TX: U4.16 (DI/T1IN), U10.3 (RXD); also elsewhere on the board

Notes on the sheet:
GND
- (leave open)
RS-232
A (non-inverting)
fitted
B (inverting)
RS-485 half duplex
MODE strap
J4 pins used
+5 V (JP8, cut to remove)
RS-485
1 = A, 2 = B, 4 = GND
J4 pin
2 = TXD, 3 = RXD, 4 = GND
CC1 / CC2 5.1k: USB device, up to 500 mA from VBUS. D4: USB VBUS -> +5V (about 4.6 V); J1 and USB may be connected together. UART_RX = MAX3160 RO AND CH340C TXD (D5, 4.7k pull-up): both host links are live; use only one at a time. UART_TX drives both.
+5 V
RS-485: fit TERM only at the two physical bus ends; fit BIAS A + BIAS B on one node only (normally the master). RS-232: REMOVE TERM, BIAS A and BIAS B (they would load TXD). D2 SM712: -7 / +12 V TVS for the bus pins. D3: 15 V bidirectional TVS for the RS-232 receiver input.
Interface
DB9 pin
open
PROTECTION, TERMINATION, BIAS, TERMINAL
TXD (output)
5, shell
HDPLX = 1 (half duplex) FAST = 0 (slew limited, <= 250 kbit/s) SHDN = 1 DE has a pull-down: the RS-485 driver stays off until firmware enables it. The RS-485 receiver is always on: firmware discards its own echo. In RS-232 mode DE drives T2OUT on J4 pin 1 (unused - leave open).
TRANSCEIVER MAX3160 (RS-232 / RS-485 multiprotocol, shared pins)
RXD (input)
USB-C SERIAL CH340C (virtual COM port on USART1, shared with the MAX3160)
